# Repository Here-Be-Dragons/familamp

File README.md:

# familamp

### Overview
---------------------
Networked lamps using a Particle Photon, WB2812B LEDs (aka NeoPixels), and a touch-sensitive panel.  They communicate and synchronize colors across lamps via the internet and Particle's cloud using Particle.subscribe() and Particle.publish() functions.  Bonus of using Particle's cloud: easily push updates and add features from Particle's browser-based IDE and Console.

### Images
---------------------
Demo of operation:  
  
https://youtu.be/uUX5NEsEXrw
  
Special mode idle sequences (instead of being off, the lamp runs an assigned idle sequence on holidays)

Circuit boards from Osh Park:

### Hardware
---------------------
-   Particle Photon
-   WB2812B strip of LEDs.  I used 60 per lamp, because this seemed like a good match for my 2A power supplies.
-   A 3.3V to 5V logic level shifter to convert the 3.3V data bus from the Particle Photon to 5V the NeoPixels require.
-   Pre-cut acrylic pieces to make the acrylic light box.  TAP Plastics was the vendor I chose for this. (See *Other Note #1*)  For each lamp:
    -   2 cut-to-size 1/8" thick pieces, 5" x 9-7/8"
	-   2 cut-to-size 1/8" thick pieces, 4-3/4" x 9-7/8"
	-   1 cut-to-size 1/8" thick piece, 5" x 5"
-   A sheet of thin copper for the top.  I used a smooth ball peen hammer on the copper before installation to give it a hammered look.
-   Wood for the base and any flourishes you want for your lamps
-   3/4" x 3/4" outside corner moulding (if desired, to hide seems).
    -   http://www.homedepot.com/p/Alexandria-Moulding-WM-206-3-4-in-x-3-4-in-x-96-in-Wood-Red-Oak-Outside-Corner-Moulding-0W206-40096C/205917014
-   Custom PCB (I designed this in EAGLE and requested manufacture by OSH Park)
-   Other supporting bits (per lamp):
	-   1 resistor of value between 300 and 500 Ohms
	-   1 resistor of value between 1MOhm and 10MOhm (See *Other Note #2*)
	-   A barrel jack of matching dimensions to your power supply (Mine were 5.5mm with a 2.1mm center pole)
	-   A 5V power supply able to power the lamp.  I chose a UL listed supply of 2A. (See *Other Note #3*)
	-   Feet for the bottom of the lamp.  I grabbed some rubber feet from my local hardware supply store.
	-   Mounting hardware to attach the PCB.  I used small screws and standoffs from my local hardware supply store.

### Software
---------------------
-   Particle's Cloud
-   NeoPixel Library: https://github.com/adafruit/Adafruit_NeoPixel (Already ported to Particle's Libraries)
-   CapSense library: https://github.com/lbt/captouch (Already ported to Particle's Libraries)

### Assembly
---------------------
-   1MOhm resistor between pins D3 and D4 of the Particle Photon
-   D2 goes to a 3.3V to 5V Logic Level Shifter, then to a resistor of value between 300 to 500 Ohms, then to the data input pin of the NeoPixels.
    -   The resistor prevents voltage spikes that might otherwise damange the first pixel in the string.
-   D3 of the Particle Photon is connected to the touch sensitive hammered copper panel on the top of the lamp.
-   Connect a capacitor (1000µF, 6.3V or higher) across VIN and GND on the Particle Photon, then connect VIN and GND to the corresponding NeoPixel pins.
    -   The 1000µF capacitor prevents the initial onrush of current from damaging the pixels over time.  I ended up using a 500µF capacitor instead so it would fit my design's physical contraints better.
-   I used a 9" length of 1" PVC pipe to wrap the NeoPixels around, and hot-glued this into a hole in the top of the wood base.
    -   Do not use hot glue to glue the NeoPixels to the PVC pipe.  Either buy the NeoPixels with 3M tape on the back or use something like silicone (do not power the pixels on until after the time indicated for complete dry time on the glue of choice to prevent shorting the pixels).  When I used hot glue, this caused the strip to stop working correctly

### Other Notes & Lessons Learned
---------------------
1.  I tried saving money here by buying a large sheet of clear acrylic and cutting it myself, then sanding to make clear into frosted.  It turns out cutting acrylic is not easy to do well.  Abandoned this idea and bought clear acrylic pre-cut from a vendor, then sanded with 60-grit using a random orbital sander to frost the acrylic.  This still took forever.  If I were to do it again, I'd just buy pre-frosted with a medium light pass-through level.
2.  A lower resistance is less sensitive, but also polls faster. A high resistance takes longer to poll but can detect changes to capacitance with more sensitivity.  Prototype between 1MOhm and 10MOhm to see what works with your design.  I chose 1m ohm because the code loops back through a the captouch poll function frequently in the middle of effect transitions. It does this to try to be responsive to touch as quickly as possible.  In really dry weather it does slow down polling significantly which has the end result of making slightly stuttery animation effects, even with 1MOhm.
3.  Try to avoid power supplies that are not UL-Listed.  2A was a good middle ground for a reliable supply.  This device draws ~1A at 5V on its brightest setting during typical usage.  If all LEDs are at maximum brightness white (not something available in the current code), the lamp draws almost 3A.

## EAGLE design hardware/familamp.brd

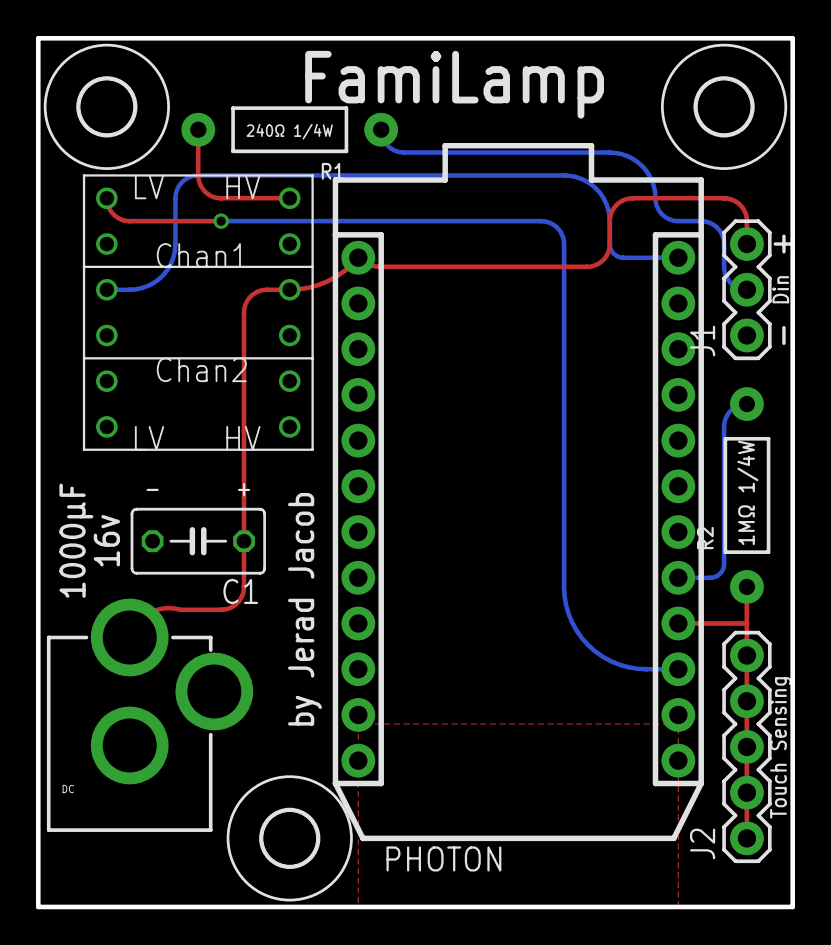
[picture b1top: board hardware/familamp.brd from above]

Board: 2 copper layers, 41.9 x 48.3 mm, 12 parts (0 on the bottom side), 8 nets.

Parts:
C1: C050-035X075
DC: POWER_JACKPTH; POWER_JACK_PTH
FRAME1: FRAME-LETTER; CREATIVE_COMMONS
J1: 1X03
J2: 1X05
PHOTON: PHOTON_WITH_HEADERS; PHOTON
R1, R2: AXIAL-0.4
U$2: LOGIC_LEVEL_CONVERTER
U$3, U$4, U$5: 3,0

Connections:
3.3V: PHOTON.24, U$2.P$3
GND: C1.2, DC.GND, DC.GNDBREAK, J1.1, PHOTON.2, PHOTON.21, U$2.P$4, U$2.P$9
unnamed: J1.2, R1.P$1
unnamed: PHOTON.17, R2.P$2
NEOHV: R1.P$2, U$2.P$12
NEOLV: PHOTON.15, U$2.P$1
TOUCH: J2.1, J2.2, J2.3, J2.4, J2.5, PHOTON.16, R2.P$1
VCC: C1.1, DC.PWR, J1.3, PHOTON.1, U$2.P$10

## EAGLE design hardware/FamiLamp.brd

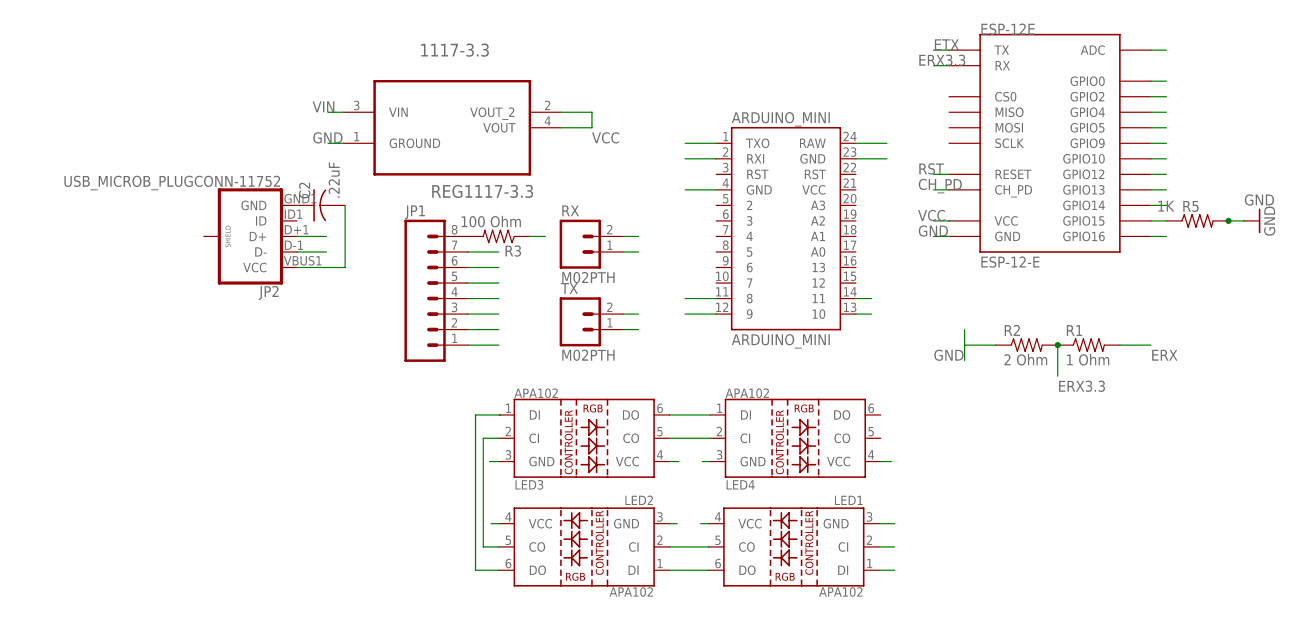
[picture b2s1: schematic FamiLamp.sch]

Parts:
1117-3.3: REG1117-3.3; SOT230P700X180-4N
ARDUINO_MINI: ARDUINO_MINI
C2: .22uF; C0603K
ESP-12E: ESP-12-E
JP1: M08; 1X08_ROUND
JP2: USB_MICROB_PLUGCONN-11752; USB-B-MICRO-SMD_V03
LED1, LED2, LED3, LED4: LED-APA102
R1: 1 Ohm; 0603-RES
R2: 2 Ohm; 0603-RES
R3: 100 Ohm; 0603-RES
R5: 1K; R0603
RX: M02PTH; 1X02
TX: M02PTH; 1X02

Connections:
ADC: ESP-12E.ADC
ARX: ARDUINO_MINI.2 (RXI), JP1.1, RX.1
ATX: ARDUINO_MINI.1 (TXO), JP1.2, TX.1
CH_PD: ESP-12E.CH_PD, R3.1
CI: ARDUINO_MINI.11 (8), LED1.2 (CI)
D10: ARDUINO_MINI.13 (10)
D11: ARDUINO_MINI.14 (11)
D+: JP2.D+1 (D+)
D-: JP2.D-1 (D-)
DI: ARDUINO_MINI.12 (9), LED1.1 (DI)
ERX: JP1.3, R1.2, TX.2
ERX3.3: ESP-12E.RX, R1.1, R2.2
ETX: ESP-12E.TX, JP1.4, RX.2
GND: 1117-3.3.1 (GROUND), ARDUINO_MINI.4 (GND), ARDUINO_MINI.23 (GND), C2.1, ESP-12E.GND, JP1.5, JP2.GND1 (GND), LED1.3 (GND), LED2.3 (GND), LED3.3 (GND), LED4.3 (GND), R2.1, R5.2
GPIO0: ESP-12E.GPIO0, JP1.6
GPIO2: ESP-12E.GPIO2
GPIO4: ESP-12E.GPIO4
GPIO5: ESP-12E.GPIO5
GPIO9: ESP-12E.GPIO9
GPIO10: ESP-12E.GPIO10
GPIO12: ESP-12E.GPIO12
GPIO13: ESP-12E.GPIO13
GPIO14: ESP-12E.GPIO14
GPIO15: ESP-12E.GPIO15, R5.1
GPIO16: ESP-12E.GPIO16
unnamed: LED2.5 (CO), LED3.2 (CI)
unnamed: LED1.6 (DO), LED2.1 (DI)
unnamed: LED1.5 (CO), LED2.2 (CI)
unnamed: LED3.5 (CO), LED4.2 (CI)
unnamed: LED3.6 (DO), LED4.1 (DI)
unnamed: JP1.8, R3.2
RST: ESP-12E.RESET
VCC: 1117-3.3.2 (VOUT_2), 1117-3.3.4 (VOUT), ESP-12E.VCC, JP1.7
VIN: 1117-3.3.3 (VIN), ARDUINO_MINI.24 (RAW), C2.2, JP2.VBUS1 (VCC), LED1.4 (VCC), LED2.4 (VCC), LED3.4 (VCC), LED4.4 (VCC)

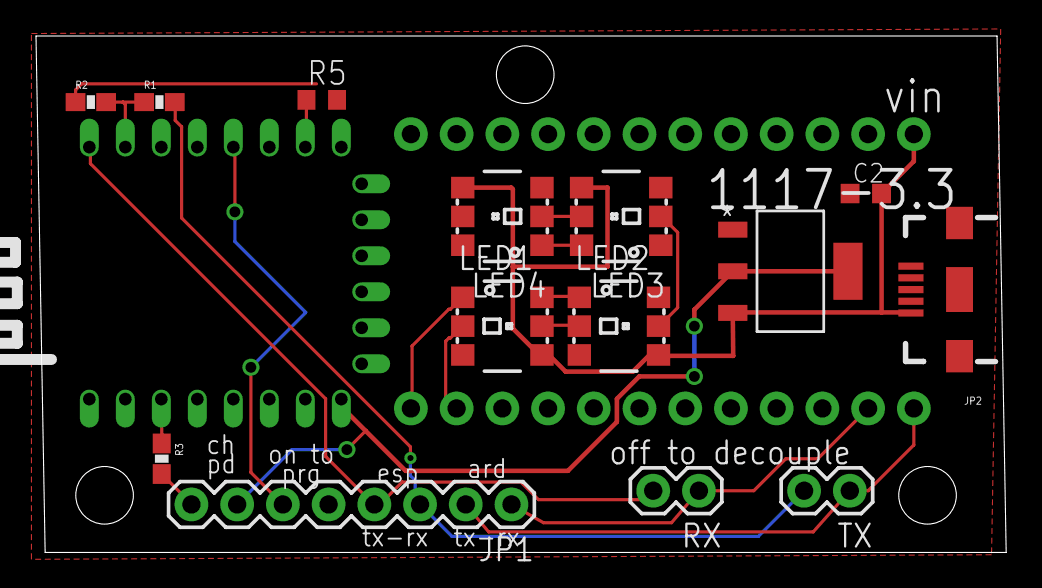
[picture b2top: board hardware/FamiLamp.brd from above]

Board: 2 copper layers, 53.9 x 28.7 mm, 16 parts (1 on the bottom side), 19 nets.

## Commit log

2016-07-12 Formatting
2016-07-12 SMB info
2016-07-12 Added image
2016-07-12 Typo
2016-07-13 Created 3D render
2016-07-13 Added 3d render
2016-07-13 Initial code commit
2016-07-13 Added CapacitiveSensor library
2016-07-13 Added assembly instructions
2016-07-13 Updated pins
2016-07-14 Clarified acrylic size
2016-07-14 Added moulding link
2016-07-15 Added paint to hardware
2016-07-16 Finished board design
2016-07-16 Board design previews
2016-07-16 Final Board Design (I HOPE)
2016-07-17 Updated TouchSensor link
2016-07-25 RUH-RUH-RUH-REWRITE
2016-07-29 Working on boot sequence
2016-08-02 Smoothing color transitions.
    Still not sure if I like the function breakout, may tweak
2016-08-02 Fixed locking issue with extinguish()
2016-08-02 Fixed CapSense link
2016-08-04 bug fix to extinguish()
2016-08-05 Down to 1 bug
    Colors smoothed and reversed to "well up" and "drain out" when touched.
2016-08-05 Final bug fixed
2016-09-05 Working snapshot
2016-12-05 Fixed the update fader
    setColor() fades properly now.
2016-12-13 Added delayed extinguish function + fixed 1 bug
    Bug: Missing
    ```activeColor = color;
    in setColor(), so activeColor never getting set.
2016-12-28 Added New Years Special Idle
    NEW FEATURES:
    Fireworks idle sequence.
    BUGFIXES:
    activePixels not setting to 0 on each touch.
2016-12-28 Clear special idle sequence day after
    NEW FEATURES:
    - Changed "New Years" to "Fireworks", also applies 4th of July
    - Lamp now dims between 8pm and 7am
    BUGFIXES:
    - Idle sequences clear (as needed) 12:00AM the following day.
    OTHER:
2016-12-28 Updated for new design direction
2017-01-07 Dusk and disco
    NEW FEATURES:
    - New Disco idle sequence
    - New Dusk mode between day and night
2017-01-10 Bugfixes to release 9
2017-01-10 Updated with images of final product
2017-01-15 Changes and updates to Release v11
    NEW FEATURES:
    - New daily easter egg color
2017-01-26 Changes and Updates to Release 12
    NEW FEATURES:
    - New Heartbeat Idle Sequence (currently not assigned)
    - New New Idle Color Flicker Sequence (St. Patty's and Valentines)
    - Adjusted brightness of a few things here and there
2017-02-09 Removed Extra Files
2017-02-09 Removed extra EAGLE files
2017-02-09 Cleanup
2017-02-09 Clarified Instructions
2017-02-10 Changes and updates to Release 13
    NEW FEATURES:
    - New setColor() does a dither instead of fade
    - Adjusted brightness of night mode
    - Idle sequences cannot be brighter than max brightness for a given time
    BUG FIXES:
    - Release 12 would not compile due to missing lines
2017-02-10 Fixed typo
2017-02-15 Partial update
2017-02-16 Improved GIF quality
    For the low, low price of 2mb
2017-03-07 Tweaks and new Easter Eggroll
    NEW FEATURES:
    - After 30 triggers in a row without going dark, trigger Easter Eggroll!
    BUG FIXES:
    - Dither now works for Easter Eggs
    OTHER:
    - Night mode now a brightness of 5, down from 20.
2017-03-09 Added easter holiday + code streamlining
    NEW FEATURES:
    - Added math to calculate easter for the current year for idleEaster().
    BUG FIXES:
    - Removed my product ID, as this is not useful for others.
    OTHER:
    - Created a onceADay() and onceAnHour() function inside loop() to limit how often certain code runs.
2017-03-18 Fix for #3
    Last pixel on lamp not updating properly due to `strip.numPixels() - 1`. Changed to `strip.numPixels()`
2017-04-10 Naming Cleanup
2017-04-10 Exclude eagle from language detection
2017-04-21 New extinguish
    NEW FEATURES:
    - New pixel-by-pixel extinguish function
    BUG FIXES:
    - Added DST offset to each timezone
    OTHER:
    - Applied DST permanently (will need to be changed for next DST change)
2017-05-15 Fixed formatting from last commit
2018-07-19 4th of July effect, sparkle on touch
2018-07-19 Generalized previous commit
2020-07-14 Updates for newer neopixel libraries

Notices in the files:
hardware/FamiLamp.brd:
© 2015
parts and their libraries:
SparkFun-Boards: Licensing: Creative Commons ShareAlike 4.0 International - https://creativecommons.org/licenses/by-sa/4.0
SparkFun-Aesthetics: Released under the Creative Commons Attribution Share-Alike 4.0 License
SparkFun-Aesthetics: https://creativecommons.org/licenses/by-sa/4.0
